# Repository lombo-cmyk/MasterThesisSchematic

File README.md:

# MasterThesisSchematic
Electrical diagram for MasterThesisApp

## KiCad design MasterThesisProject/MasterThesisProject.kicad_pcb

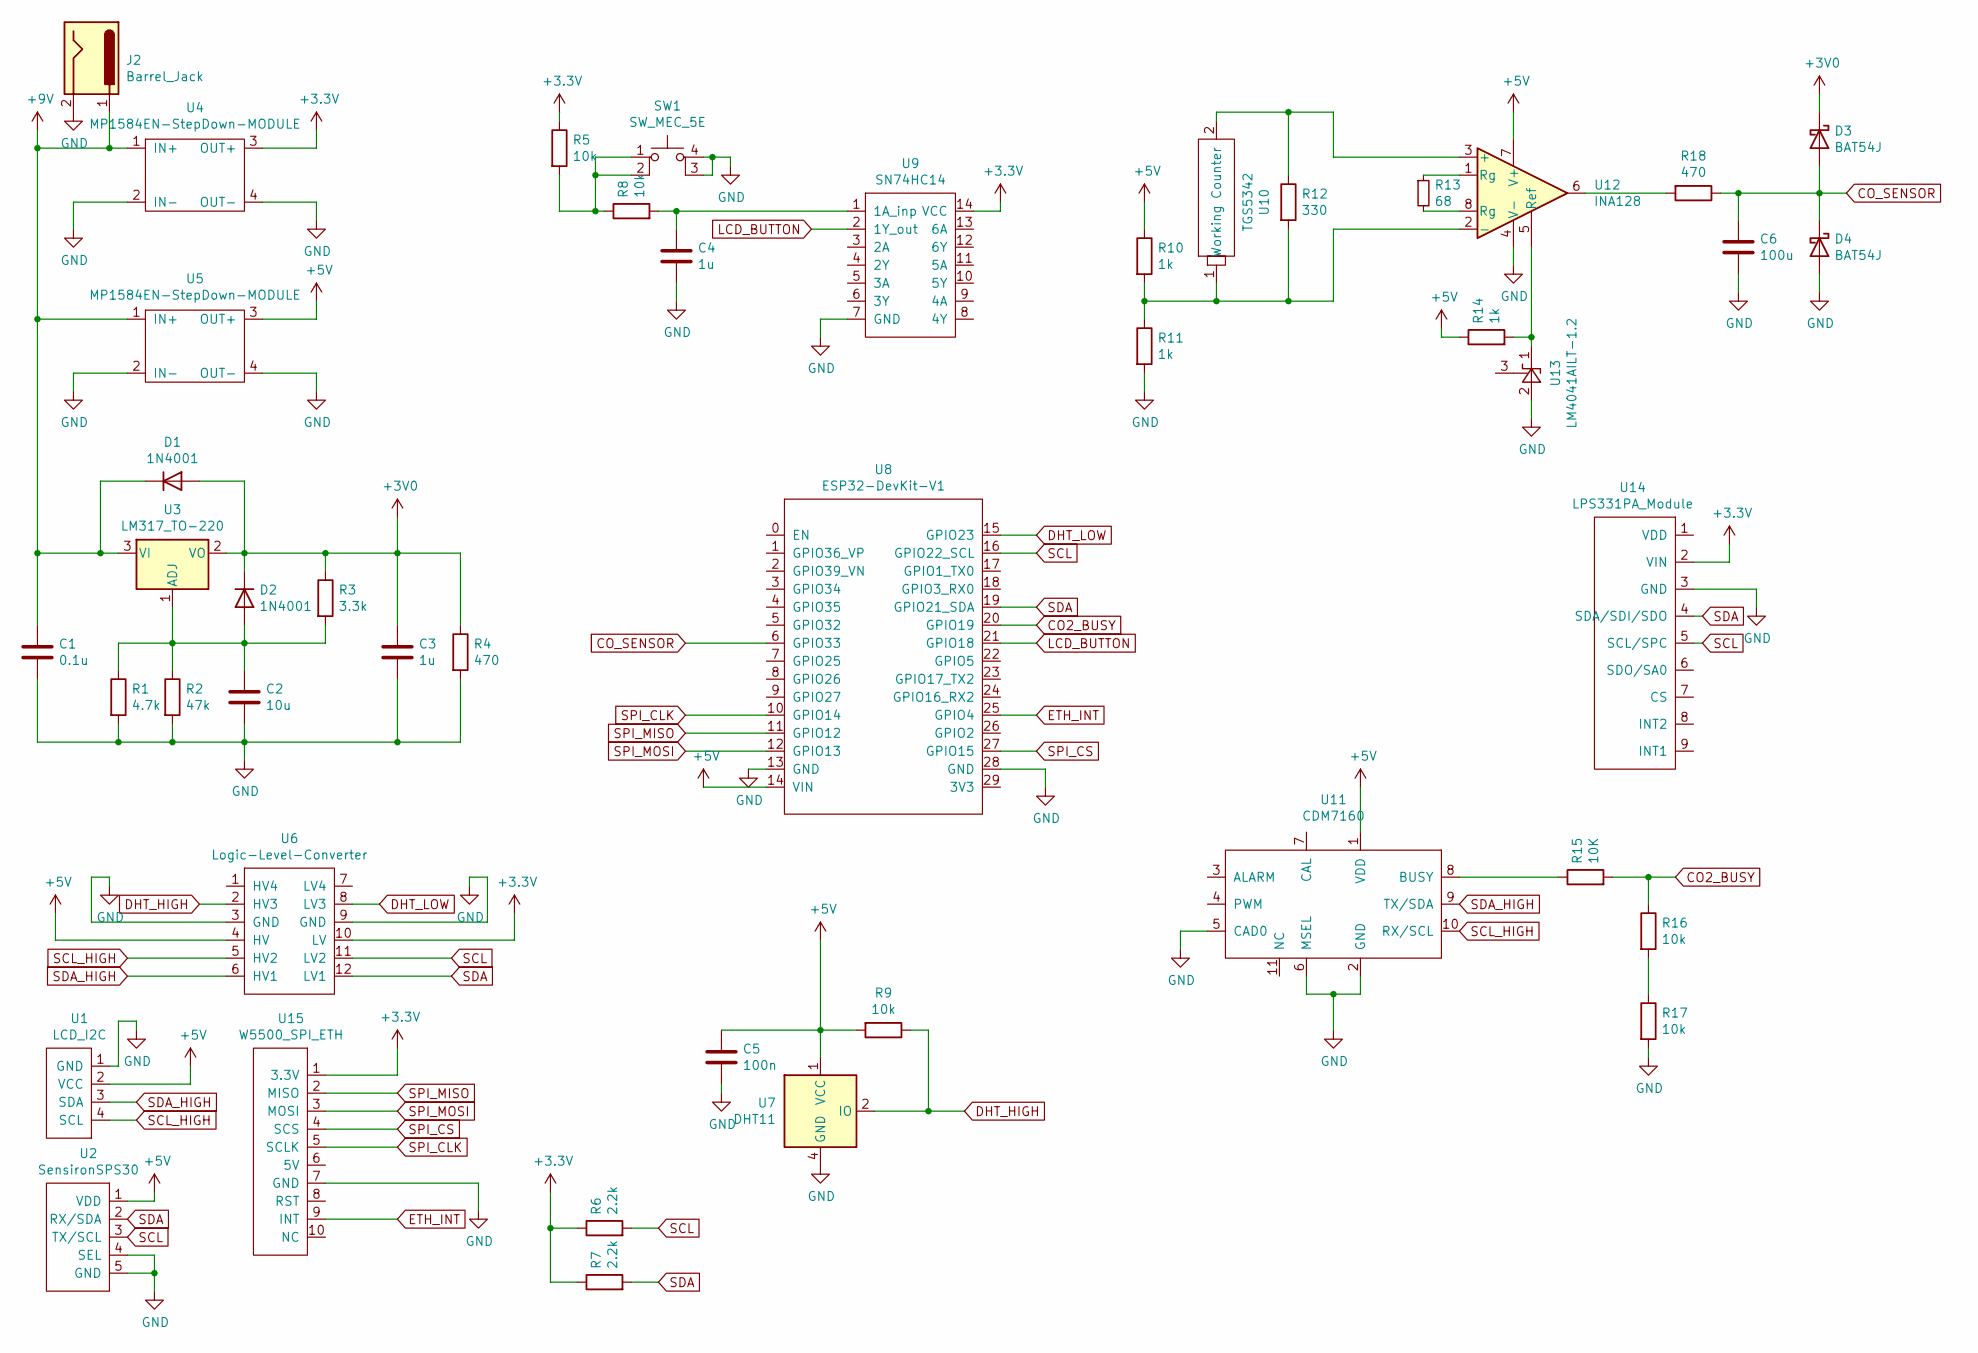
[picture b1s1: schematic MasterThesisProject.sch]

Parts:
C1: 0.1u; C_0805_2012Metric_Pad1.18x1.45mm_HandSolder
C2: 10u; C_0805_2012Metric_Pad1.18x1.45mm_HandSolder
C3, C4: 1u; C_0805_2012Metric_Pad1.18x1.45mm_HandSolder
C5: 100n; C_0805_2012Metric_Pad1.18x1.45mm_HandSolder
C6: 100u; C_0805_2012Metric_Pad1.18x1.45mm_HandSolder
D1, D2: 1N4001; D_DO-41_SOD81_P10.16mm_Horizontal
D3, D4: BAT54J; D_SOT-23_ANK
J2: Barrel_Jack; PinSocket_1x02_P2.54mm_Vertical
R1: 4.7k; R_0805_2012Metric_Pad1.20x1.40mm_HandSolder
R2: 47k; R_0805_2012Metric_Pad1.20x1.40mm_HandSolder
R3: 3.3k; R_0805_2012Metric_Pad1.20x1.40mm_HandSolder
R4, R18: 470; R_0805_2012Metric_Pad1.20x1.40mm_HandSolder
R5, R8, R9, R16, R17: 10k; R_0805_2012Metric_Pad1.20x1.40mm_HandSolder
R6, R7: 2.2k; R_0805_2012Metric_Pad1.20x1.40mm_HandSolder
R10, R11, R14: 1k; R_0805_2012Metric_Pad1.20x1.40mm_HandSolder
R12: 330; R_0805_2012Metric_Pad1.20x1.40mm_HandSolder
R13: 68; R_0805_2012Metric_Pad1.20x1.40mm_HandSolder
R15: 10K; R_0805_2012Metric_Pad1.20x1.40mm_HandSolder
SW1: SW_MEC_5E; PinSocket_1x04_P2.54mm_Vertical
U1: LCD_I2C; PinHeader_1x04_P2.54mm_Vertical
U2: SensironSPS30; PinHeader_1x05_P2.54mm_Vertical
U3: LM317_TO-220; TO-220-3_Vertical
U4, U5: MP1584EN-StepDown-MODULE; MP2307_module
U6: Logic-Level-Converter
U7: DHT11; Aosong_DHT11_5.5x12.0_P2.54mm
U8: ESP32-DevKit-V1; ESP_DEVKIT_V1_30_PIN
U9: SN74HC14; DIP-14_W7.62mm
U10: TGS5342; TGS_5342
U11: CDM7160
U12: INA128; SOIC-8_3.9x4.9mm_P1.27mm
U13: LM4041AILT-1.2; SOT-23
U14: LPS331PA_Module; LPS331AP_Module
U15: W5500_SPI_ETH

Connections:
+3V0: C3.1, D1.2 (A), D2.1 (K), D3.1 (K), R3.1, R4.1, U3.2 (VO)
+3V3: R5.1, R6.1, R7.1, U4.3 (OUT+), U6.10 (LV), U9.14 (VCC), U14.2 (VIN), U15.1 (3.3V)
+5V: C5.1, R9.2, R10.1, R14.1, U1.2 (VCC), U2.1 (VDD), U5.3 (OUT+), U6.4 (HV), U7.1 (VCC), U8.14 (VIN), U11.1 (VDD), U12.7 (V+)
+9V: C1.1, D1.1 (K), J2.1, U3.3 (VI), U4.1 (IN+), U5.1 (IN+)
CO2_BUSY: R15.2, R16.1, U8.20 (GPIO19)
CO_SENSOR: C6.1, D3.2 (A), D4.1 (K), R18.1, U8.6 (GPIO33)
DHT_HIGH: R9.1, U6.2 (HV3), U7.2 (IO)
DHT_LOW: U6.8 (LV3), U8.15 (GPIO23)
ETH_INT: U8.25 (GPIO4), U15.9 (INT)
GND: C1.2, C2.2, C3.2, C4.2, C5.2, C6.2, D4.2 (A), J2.2, R1.2, R2.2, R4.2, R11.2, R17.2, SW1.3 (K), SW1.4 (A), U1.1 (GND), U2.4 (SEL), U2.5 (GND), U4.2 (IN-), U4.4 (OUT-), U5.2 (IN-), U5.4 (OUT-), U6.3 (GND), U6.9 (GND), U7.4 (GND), U8.13 (GND), U8.28 (GND), U9.7 (GND), U11.2 (GND), U11.5 (CAD0), U11.6 (MSEL), U12.4 (V-), U13.2 (A), U14.3 (GND), U15.7 (GND)
LCD_BUTTON: U8.21 (GPIO18), U9.2 (1Y_out)
unnamed: C2.1, D2.2 (A), R1.1, R2.1, R3.2, U3.1 (ADJ)
unnamed: C4.1, R8.2, U9.1 (1A_inp)
unnamed: R5.2, R8.1, SW1.1, SW1.2
unnamed: R10.2, R11.1, R12.2, U10.1 (Working), U12.2 (-)
unnamed: R12.1, U10.2 (Counter), U12.3 (+)
unnamed: R13.1, U12.1 (Rg)
unnamed: R13.2, U12.8 (Rg)
unnamed: R14.2, U12.5 (Ref), U13.1 (K)
unnamed: R15.1, U11.8 (BUSY)
unnamed: R16.2, R17.1
unnamed: R18.2, U12.6
SCL: R6.2, U2.3 (TX/SCL), U6.11 (LV2), U8.16 (GPIO22_SCL), U14.5 (SCL/SPC)
SCL_HIGH: U1.4 (SCL), U6.5 (HV2), U11.10 (RX/SCL)
SDA: R7.2, U2.2 (RX/SDA), U6.12 (LV1), U8.19 (GPIO21_SDA), U14.4 (SDA/SDI/SDO)
SDA_HIGH: U1.3 (SDA), U6.6 (HV1), U11.9 (TX/SDA)
SPI_CLK: U8.10 (GPIO14), U15.5 (SCLK)
SPI_CS: U8.27 (GPIO15), U15.4 (SCS)
SPI_MISO: U8.11 (GPIO12), U15.2 (MISO)
SPI_MOSI: U8.12 (GPIO13), U15.3 (MOSI)

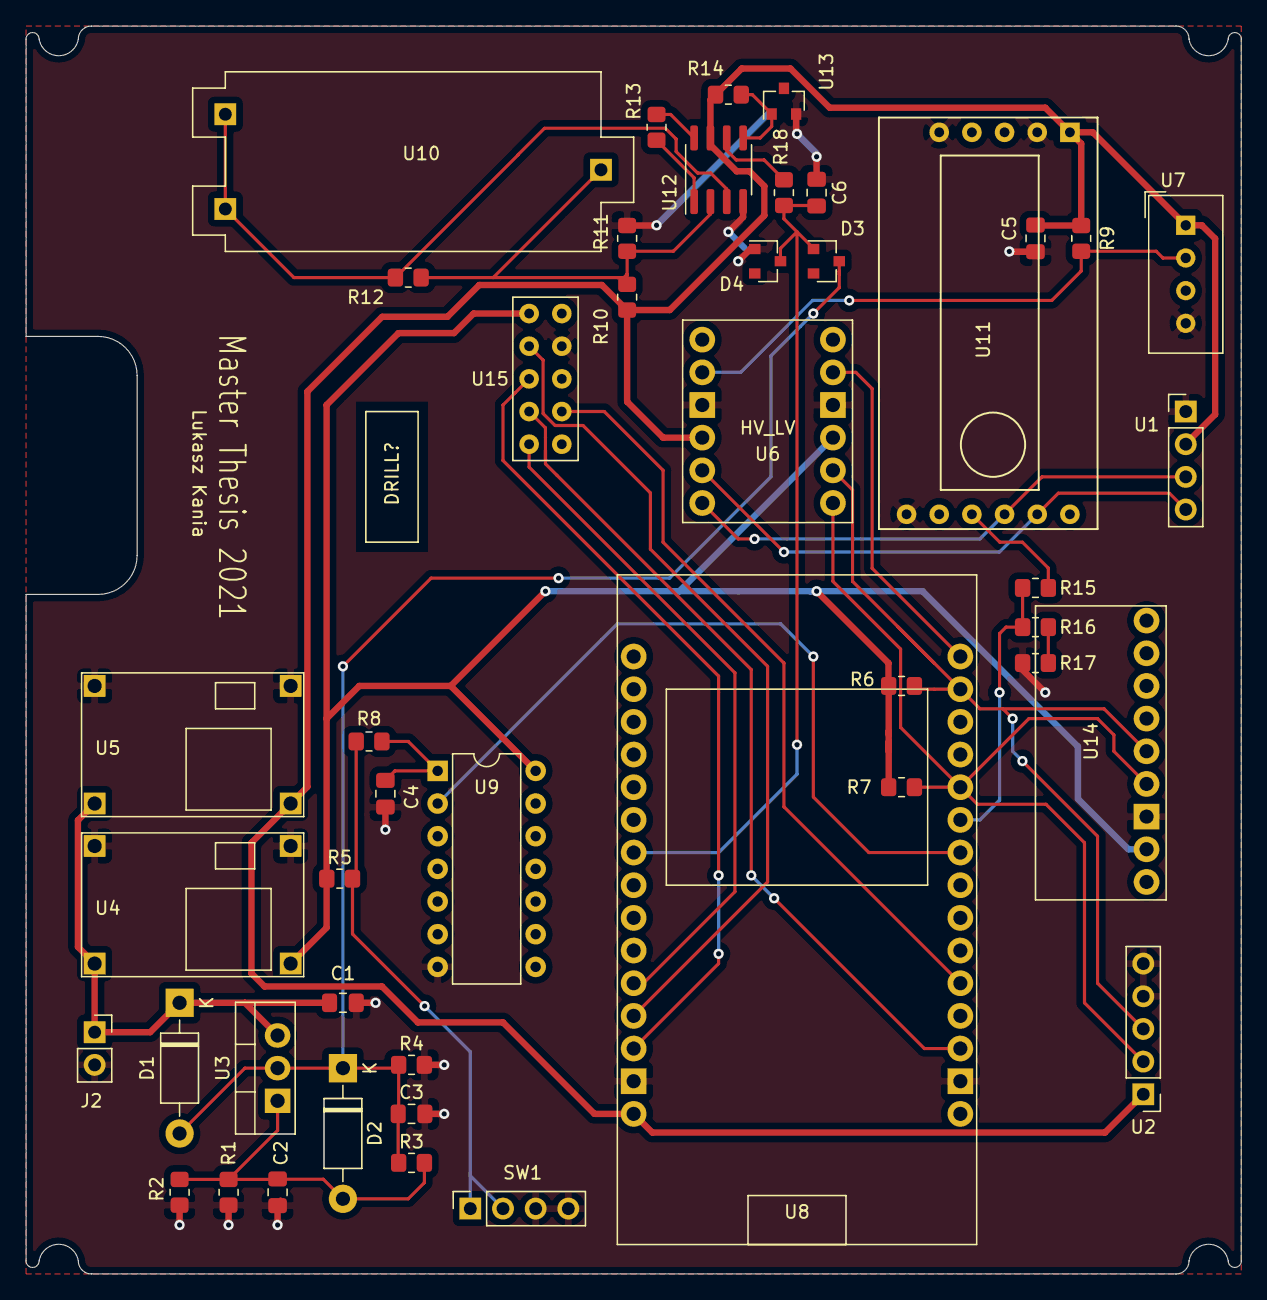
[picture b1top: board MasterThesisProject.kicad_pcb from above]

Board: 2 copper layers, 94.5 x 97.0 mm, 45 parts (0 on the bottom side), 30 nets.

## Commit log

2021-03-03 Add cystom common symbols lib
2021-03-03 Add empty project
2021-03-16 Put most of the devices on the schematic
2021-03-17 Add some electrical connections to the schematic
2021-03-17 Add more connections to schematic
2021-03-17 Update CDM7160, put new at the schematic
2021-03-20 Add connections to CDM7160, finish SDA/SCL lines
2021-03-20 Add Carbon Monoxide sensor connections
2021-03-20 Add DHT22 to the schematic
2021-04-13 Update CO resistor value
2021-04-17 Add 3.0V source, update CO diodes
2021-04-17 Add spi_eth and co_sensor connections to schematic
2021-04-17 Add footprints to resistors
2021-04-17 Add footprint to esp
2021-04-18 Add footprints to all elements
2021-04-18 Add init version of components locations
2021-04-18 Connect all elements to GND, minor updates to schematic
2021-04-19 Add all missing connections to pcb
2021-04-24 Add new pcb edges
2021-04-25 Update edges
2021-04-25 Update W5500 schematic and PCB to match custom PCB connectino
2021-04-25 Remove old pcb, port elements to new one
2021-04-25 Add all paths, copper layers etc
2021-04-25 Add signature to PCB, generate gerber files
2021-05-02 Modify .gitignore to omit BOM files
